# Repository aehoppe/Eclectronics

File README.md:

# Eclectronics

Repo for designs from ENGR3430 Eclectronics Fall 2017

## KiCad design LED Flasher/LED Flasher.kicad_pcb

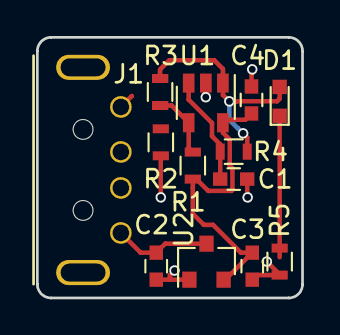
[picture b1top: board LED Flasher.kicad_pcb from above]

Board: 2 copper layers, 14.7 x 14.5 mm, 13 parts (0 on the bottom side), 7 nets.

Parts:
C1, C2: 10uF 5%; C_0603
C3: 1uF 5%; C_0603
C4: 0.1uF 5%; C_0603
D1: LED; LED_0603
J1: USB_A; USB_A_480370001
R1, R2: 20K 1%; R_0603
R3: 10K 1%; R_0603
R4: 40.2K 1%; R_0603
R5: 3.01K 1%; R_0603
U1: MCP6021; SOT-23-5
U2: MCP1702-3302E; SOT-23

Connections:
+3V3: C3.1, C4.2, R1.2, U1.5, U2.2
/S_out: D1.2, R3.1, R4.1, U1.1
GND: C1.2, C2.2, C3.2, C4.1, J1.4, J1.5, R2.2, R5.2, U1.2, U2.1
unnamed: C1.1, R4.2, U1.3
unnamed: D1.1, R5.1
unnamed: R1.1, R2.1, R3.2, U1.4
VBUS: C2.1, J1.1, U2.3

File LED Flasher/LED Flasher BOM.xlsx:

Component | Count: | 13
Ref | Value | Description | Digikey Catalog #
C1 | 10uF | CAP CER 10UF 16V X7R 0805 | 1276-2872-1-ND
C2 | 10uF | CAP CER 10UF 16V X7R 0805 | 1276-2872-1-ND
C3 | 1uF | CAP CER 1UF 25V X7R 0603 | 399-7376-1-ND
C4 | 0.1uF | CAP CER 0.1UF 50V X7R 0603 | 311-1779-1-ND
D1 | LED | LED GREEN CLEAR 0805 SMD | 160-1887-1-ND
J1 | USB_A | CONN PLUG USB 4POS RT ANG PCB | WM17117-ND
R1 | 20K | RES SMD 20K OHM 1% 1/10W 0603 | 311-20.0KHRCT-ND
R2 | 20K | RES SMD 20K OHM 1% 1/10W 0603 | 311-20.0KHRCT-ND
R3 | 10K | RES SMD 10K OHM 1% 1/10W 0603 | 311-10.0KHRCT-ND
R4 | 40.2K | RES SMD 40.2K OHM 1% 1/10W 0603 | 311-40.2KHRCT-ND
R5 | 3.01K | RES SMD 30.1K OHM 1% 1/10W 0603 | 311-30.1KHRCT-ND
U1 | MCP6021 | IC OPAMP GP 10MHZ RRO SOT23-5 | MCP6021T-E/OTCT-ND
U2 | MCP1702-3302E | IC REG LIN 3.3V 250MA SOT23A-3 | MCP1702T-3302E/CBCT-ND

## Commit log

2017-09-20 Added readme
2017-09-20 Create LICENSE
2017-09-20 Added LED flasher project
